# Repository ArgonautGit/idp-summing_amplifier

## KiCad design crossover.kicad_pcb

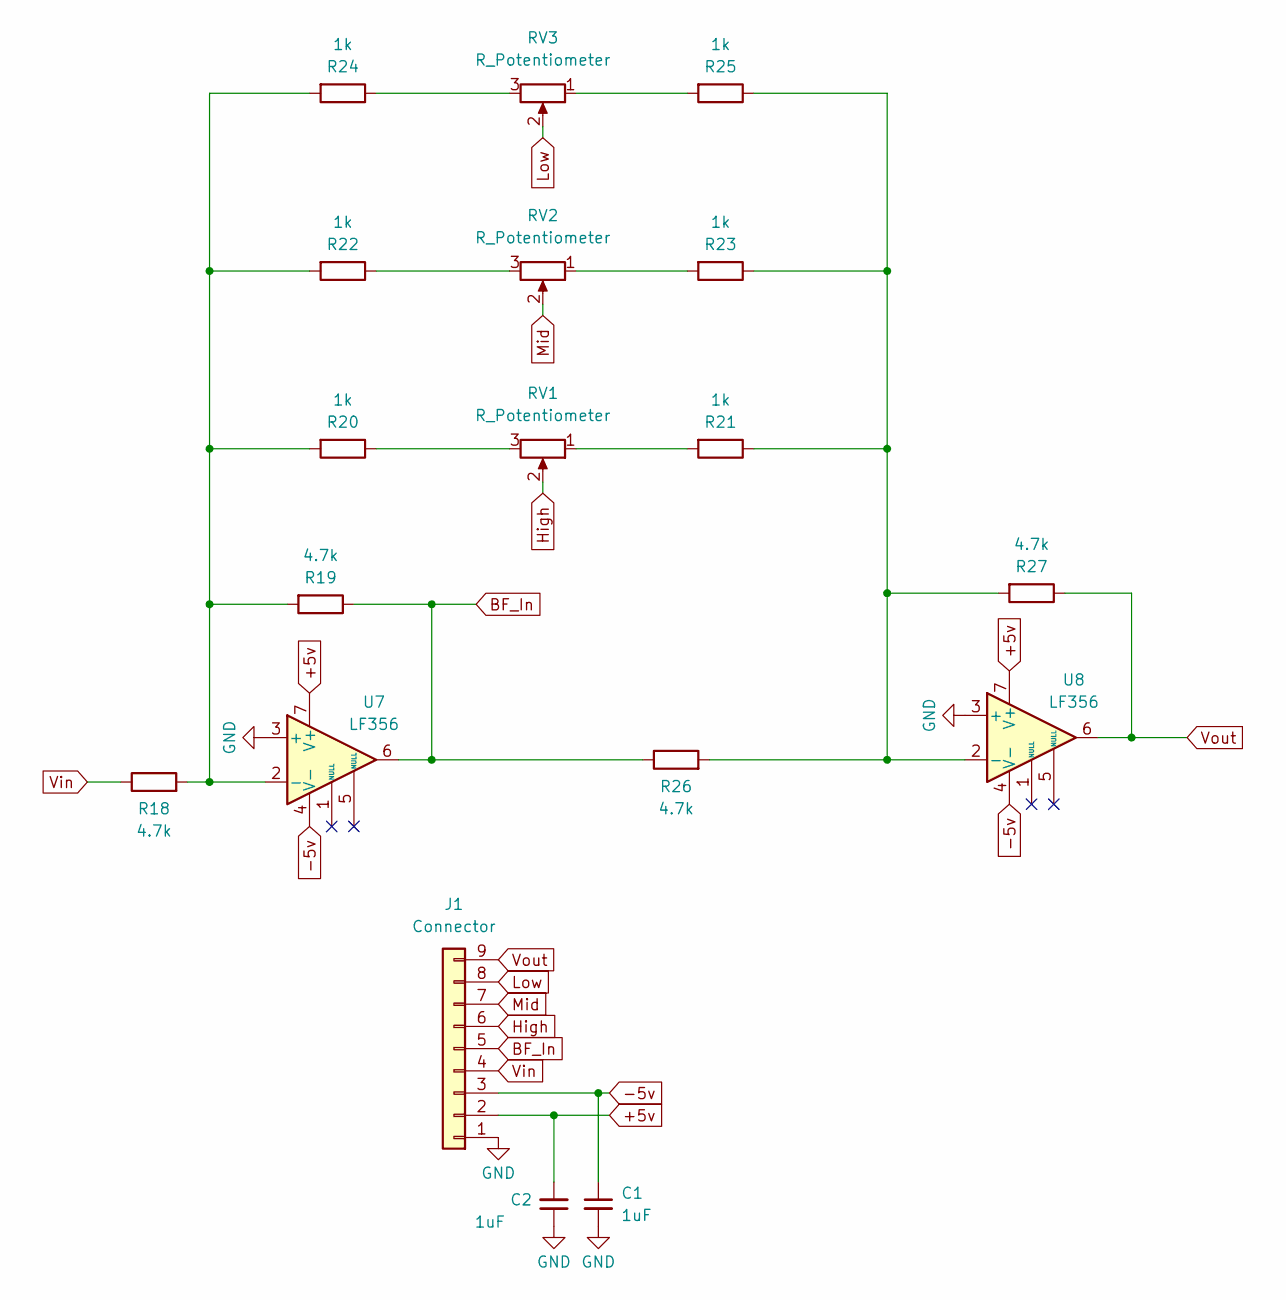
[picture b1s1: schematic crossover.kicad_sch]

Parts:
C1, C2: 1uF; C_1206_3216Metric_Pad1.33x1.80mm_HandSolder
J1: Connector; JST_PH_B9B-PH-K_1x09_P2.00mm_Vertical
R18, R19, R26, R27: 4.7k; R_0805_2012Metric_Pad1.20x1.40mm_HandSolder
R20, R21, R22, R23, R24, R25: 1k; R_0805_2012Metric_Pad1.20x1.40mm_HandSolder
RV1, RV2, RV3: R_Potentiometer; Potentiometer_Piher_PT-6-V_Vertical
U7, U8: LF356; DIP-8_W7.62mm_LongPads

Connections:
+5v: C2.2, J1.2, U7.7 (V+), U8.7 (V+)
-5v: C1.1, J1.3, U7.4 (V-), U8.4 (V-)
BF_In: J1.5, R19.1, R26.1, U7.6
GND: C1.2, C2.1, J1.1, U7.3 (+), U8.3 (+)
High: J1.6, RV1.2
Low: J1.8, RV3.2
Mid: J1.7, RV2.2
unnamed: R20.1, RV1.3
unnamed: R21.2, RV1.1
unnamed: R22.1, RV2.3
unnamed: R23.2, RV2.1
unnamed: R24.1, RV3.3
unnamed: R25.2, RV3.1
unnamed: R18.2, R19.2, R20.2, R22.2, R24.2, U7.2 (-)
unnamed: R21.1, R23.1, R25.1, R26.2, R27.2, U8.2 (-)
Vin: J1.4, R18.1
Vout: J1.9, R27.1, U8.6

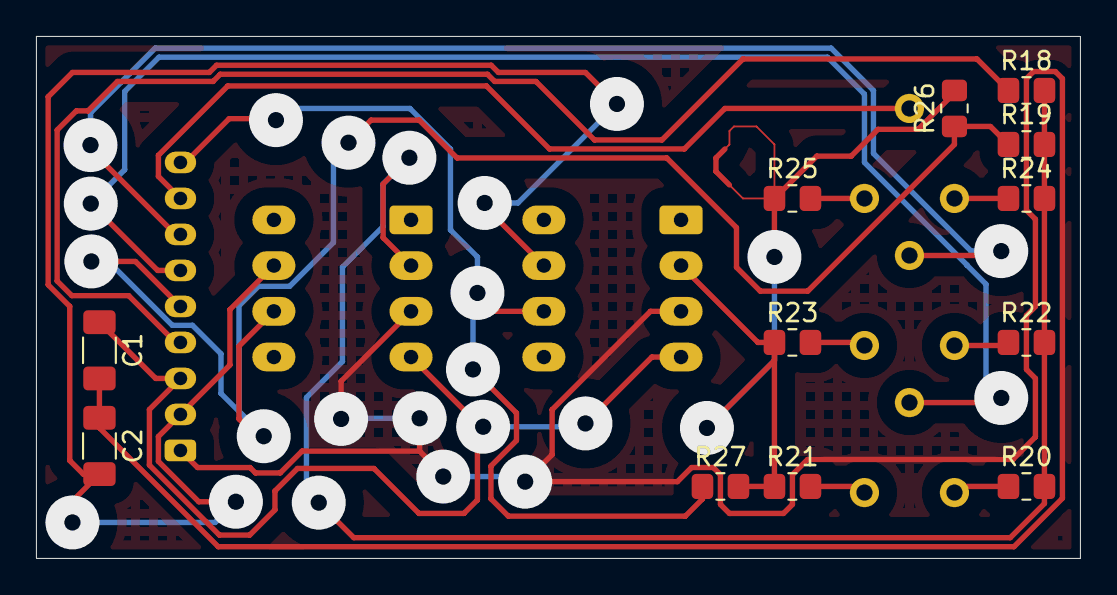
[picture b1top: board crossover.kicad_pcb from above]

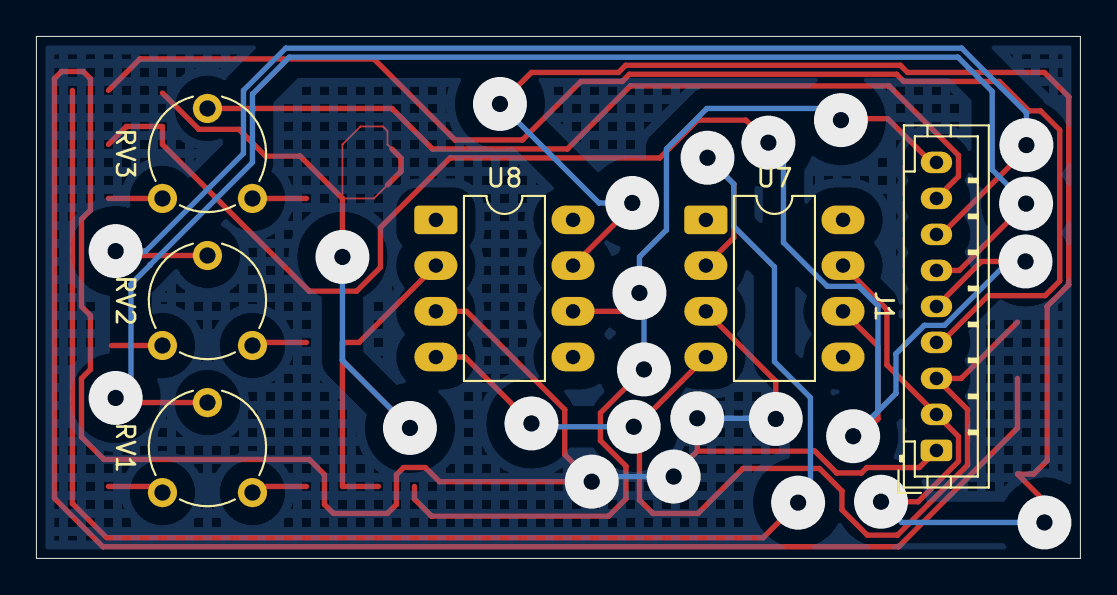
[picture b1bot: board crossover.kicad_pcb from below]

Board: 2 copper layers, 58.0 x 29.0 mm, 18 parts (6 on the bottom side), 17 nets.

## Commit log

2025-11-25 init
2025-11-25 Added JST
